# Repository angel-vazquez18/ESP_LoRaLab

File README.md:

# ESP_LoraLab

One repository for the ESP-IDF node firmware and the macOS LoRa laboratory testbed.
One or two physical nodes share one firmware codebase; the host assigns roles A/B.
Local checks work with either node alone. RF tests require two distinct devices.
The dashboard and CLI use the same Python backend and experiment lifecycle.

```text
ESP_LoraLab/
├── AGENTS.md                  Start here for agent-assisted work
├── CONTEXT.md                 Shared domain vocabulary
├── contracts/v2/              Shared defaults, vectors and generated wire schemas
├── firmware/
│   ├── lora_node/             Main node control, health and finite memory diagnostics
│   ├── diagnostic/            Working serial/health diagnostic target
│   └── components/            Planned shared firmware module locations
├── testbed/
│   ├── src/lora_testbed/       Python backend, CLI, physical sessions and analysis
│   ├── frontend/              React/TypeScript dashboard
│   ├── tests/                 Host, procedure and adapter regression checks
│   └── pyproject.toml         Python project and dependency lock beside it
├── hardware/                  Planned wiring, board profile and reference diagram
├── docs/                      Architecture, status, CDR, contracts and procedures
├── scripts/                   Shared generation and verification tools
└── local/                     Ignored local migration artifacts, if present
```

## Start the host

From this repository root:

```sh
make setup
make frontend
make serve
```

Open http://127.0.0.1:8000. For dashboard development use `make frontend-dev`
in another terminal while the backend runs. Requires Python 3.12+, uv and Node/npm.
The host's ignored data directory is `testbed/data/` when started with `make serve`.
Use one backend per data directory and release serial ports before IDF Monitor.

Individual commands from the repository root:

```sh
uv run --project testbed lora-testbed status
uv run --project testbed lora-testbed serial-check --preview
uv run --project testbed lora-testbed preflight IF-02
uv run --project testbed lora-testbed serial-check --role A
```

The host has no simulation mode. Connect each node from Bench overview. The
physical diagnostic check covers only part of IF-01; other experiment runners
remain blocked pending firmware and physical execution support. Historical
records retain their original provenance and exports.

## Build firmware

ESP-IDF v6.0.2, target ESP32-S3. Activate your local installation first:

```sh
source /Users/anken18/.espressif/v6.0.2/esp-idf/export.sh
make firmware-build
```

`make diagnostic-build` builds the existing diagnostic target. These targets only
build; flashing is a separate operator action. Main firmware includes strict serial
control, finite diagnostics, artifact/audio/codec operations and protected finite
radio messages. Board selections and exact live capabilities gate their use;
physical acceptance is still required. See [Milestone 1 review](docs/milestone_1_review.md) and the
[firmware guide](firmware/README.md).

## Verify

```sh
make check
```

This runs all host tests, Ruff, the dashboard production build, generated-contract
consistency and the repository checks. Firmware builds are separate toolchain
checks. See [development workflow](docs/development.md) for exact commands.

## Read next

- [Agent instructions and task routing](AGENTS.md) and [document ownership](docs/agent_workflow.md)
- [Architecture](docs/architecture.md) and [shared vocabulary](CONTEXT.md)
- [GitHub board, issues and acceptance workflow](docs/github_workflow.md)
- [Node development plan](docs/node_development_plan.md): capabilities, milestones and completion evidence
- [Project brief and confirmed decisions](docs/project_brief.md)
- [Current status](docs/status.md) and [23-experiment implementation checklist](docs/experiment_implementation_checklist.md)
- [Hardware wiring](hardware/README.md)
- [Migration and retained local artifacts](docs/migration.md)

The shared local codec API/CLI now preserves source, encoded and decoded files
with independent verification and playback provenance. See
[local codec workflow](docs/codec_provenance.md) for commands and physical checks.

Secure finite voice from a reference or microphone is now available through the
shared Voice dashboard, API and CLI, with labelled equal-encoded-size and
standard64 comparisons.
See [secure voice workflows](docs/secure_voice_workflows.md) for readiness,
commands, retained files and remaining physical acceptance.

Optional [host-armed PTT capture](docs/host_armed_ptt.md) defaults off. Confirm the
printed board revision and GPIO47-to-GND wiring before enabling a physical image.

Optional [OLED status](docs/oled_status.md) shows real node phases through an
isolated worker. It defaults off and requires a verified standard V4 R2
OLED/power map; its USB observation does not qualify physical screen output.

Data and committed encoded voice share the [reserved run lifecycle](docs/run_lifecycle.md):
prepare reserves working memory, both roles arm, sender start has a five-second
window, and cleanup preserves original errors and committed evidence. New RF work
requires matching `finite_message_execution_v3` host/firmware profiles.

Optional [named memory observations](docs/memory_observations.md) collect bounded
10 Hz and stage samples with separate observed minima, requested buffer ownership
and explicit missed/dropped/untracked limits. Physical memory acceptance is pending.

The [fixed-rate encoded source](docs/fixed_rate_source.md) independently produces
8 bytes per 20 ms, bounds all encoded queue content to 4,800 bytes and preserves
actual pacing/drop/drain evidence. It reuses protected multi-message transport;
host procedure controls and sustained-link qualification follow separately.

The [common physical lifecycle](docs/common_physical_lifecycle.md) binds data,
audio/files and diagnostic jobs to an exact USB connection as well as device/boot.
It retains primary versus cleanup failures, committed captures after readback
failure, and durable diagnostic summaries/evidence without automatic resume.

[Physical campaign plans](docs/physical_campaign_plans.md) save typed settings,
repetitions, directions and seeded order with linked batches bounded to 64 cases
and 30 minutes. Preview/save/list/reload work through the API and CLI; campaign
execution and its dashboard remain separate following work.

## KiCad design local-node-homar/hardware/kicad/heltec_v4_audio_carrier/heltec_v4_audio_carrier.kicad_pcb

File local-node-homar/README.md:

# LoRa walkie-talkie

An ESP32 project that records a short voice message, splits it into small packets,
reassembles the packets, and plays the message through a speaker. This is the
audio foundation for a LoRa walkie-talkie.

**Current stage: bringing up two Heltec WiFi LoRa 32 V4.3 / ESP32-S3R2 nodes.**
Packet delivery is still simulated in memory; the firmware does not transmit
over LoRa yet. PTT is deferred until the radio transport works. The Heltec audio
bench holds the SX1262 in reset and disables its RF front end.

### Heltec bench targets

| Node / OLED label | Assigned port | Hardware base MAC | PlatformIO environment |
| --- | --- | --- | --- |
| Heltec-A / COM6 | COM6 | 8C:FD:49:B5:B7:8C | `heltec_v4_com6` |
| Heltec-B / COM7 | COM7 | 44:1B:F6:6F:99:E4 | `heltec_v4_com7` |

Both chips were identified through their ROM bootloader as ESP32-S3 revision
0.2 with 2 MB embedded quad PSRAM and 16 MB flash. COM names are Windows
assignments and can change; match the USB serial number to the MAC above before
uploading. The firmware's OLED label records the assigned bench port.

The default build now selects both Heltec targets. Each uses Rev B wiring:
microphone BCLK/WS/data = GPIO4/6/38; amplifier BCLK/LRC/DIN/SD = GPIO40/41/47/48.
Amplifier SD needs its 1 kOhm pulldown; VIN uses USB 5V. Leave GPS disconnected
and GPIO39/PTT unwired. The built-in OLED uses SDA17/SCL18/reset21 with Vext36;
no external display wiring is needed. These assignments are for standard R2,
not V4-R8.

Current wiring reference: [Rev B schematic](output/schematics/Heltec_V4_R2_Wiring_RevB.svg)
([PNG](output/schematics/Heltec_V4_R2_Wiring_RevB.png)). The original Heltec PDF
and earlier drawings are historical drafts. Heltec speaker output is still
unresolved; the latest checkpoint and remaining connection checks are recorded
in [BENCH_VALIDATION.md](BENCH_VALIDATION.md).

On ESP32-S3, speaker output uses 32-bit stereo I2S slots at 512 kHz BCLK,
with the same 16-bit PCM promoted into the upper 16 bits of each slot. Silent
clocks run before amplifier enable. This avoids the MAX98357A's special 256 kHz
startup mode, which conflicts with the S3 serializer's stopped WS-high state.
The original ESP32 keeps its existing 16-bit stereo / 256 kHz sequence.

```powershell
pio run -e heltec_v4_com6 -e heltec_v4_com7
pio run -e heltec_v4_com6 -t upload
pio run -e heltec_v4_com7 -t upload
python tools/verify_heltec_bench.py --ports COM6 COM7
```

The verification tool keeps both serial connections open, checks identity and
audio readiness, then plays a one-second 1 kHz tone on A, on B, and on both.
It saves per-port logs and a JSON summary under `captures/`. Successful serial
completion proves the digital transfer; listening is still needed to confirm
sound from each speaker. Close other serial monitors before running it.

For silent-speaker diagnosis, the diagnostic firmware adds `v` to report GPIO48
enable readback and measured GPIO40/41 clock-edge counts. After uploading that
build, use `python tools/verify_heltec_bench.py --identify-only --probe-pins`.
Expected clocks are approximately 512 kHz BCLK and 8 kHz LRC, with SD high.
These are measurements at the ESP32 pins; they do not prove the wires reach the
amplifier or that its VIN supply is present. `--tone-repetitions 3` repeats each
node's one-second tone three times before the paired test.

The Heltec `s` tone also reports DIN rising-edge activity on GPIO47. An intact
one-second test pattern has 32,000 rising edges (two transitions per 32-bit
word, two slots per frame, 8,000 frames). This count checks MCU output activity;
it does not decode I2S timing or verify the waveform at the amplifier terminal.
Playback pads its last DMA block with silence to keep subsequent commands on a
descriptor boundary. This avoids losing initial samples after an idle interval;
the requested audio samples and tone duration are unchanged.

For scope capture, firmware revision `audio-bench-7-scope-tone` adds `b` for a
continuous 15-second 1 kHz tone. Use
`python tools/verify_heltec_bench.py --ports COM7 --tone-seconds 15`, or send `b`
through a 115200-baud serial monitor. This revision is uploaded to COM7; COM6
still has the preceding diagnostic revision. The usual `s` remains one second.

Use `pio run -e esp32dev` for the original ESP-WROOM-32 setup described below;
its GPIO assignments remain unchanged. Never upload that binary to a Heltec.

The original hardware setup uses an **ESP-WROOM-32 development board**, an **INMP441
microphone**, and a **MAX98357A amplifier**. The firmware records three-second
clips. On 2026-11-16, the user confirmed clear recorded speech, working speaker
playback, packetized playback, and playback with simulated packet loss. Saved
captures passed format and checksum checks with no clipped samples. One capture
still contains a large low-frequency disturbance; amplifier startup timing also
remains unmeasured. See the latest checkpoint in [BENCH_VALIDATION.md](BENCH_VALIDATION.md).
Successful compilation alone does not establish that the audio hardware works.

Start with sections 1–3 for your first build. Continue with hardware when ready.

- [1. Install the tools](#1-install-the-tools)
- [2. Fork or clone the repository](#2-fork-or-clone-the-repository)
- [3. Build the firmware](#3-build-the-firmware)
- [4. Connect and check the hardware](#4-connect-and-check-the-hardware)
- [5. Upload and try the commands](#5-upload-and-try-the-commands)
- [6. Save recordings on your computer](#6-save-recordings-on-your-computer)
- [7. Run the tests](#7-run-the-tests)
- [8. Find your way around the code](#8-find-your-way-around-the-code)
- [9. Make and contribute a change](#9-make-and-contribute-a-change)
- [Troubleshooting](#troubleshooting)
- [Additional documentation](#additional-documentation)

## 1. Install the tools

You will need an internet connection for the initial downloads and these tools:

| Tool | What it is for |
| --- | --- |
| [Git](https://git-scm.com/install/) | Downloads the repository and records changes to files. |
| [Visual Studio Code](https://code.visualstudio.com/) | The editor used by this guide. |
| [PlatformIO IDE](https://marketplace.visualstudio.com/items?itemName=platformio.platformio-ide) | A VS Code extension that installs the ESP32 build tools and builds/uploads firmware. |
| A GitHub account with repository access | Lets you clone this private repository and contribute changes. |

In VS Code, open **Extensions** with **Ctrl+Shift+X**, search for **PlatformIO
IDE**, and install the extension published by PlatformIO. Allow its setup to
finish, then restart VS Code if prompted. PlatformIO Core, the `pio` command-line
tool, is included with the extension. See the
[official installation guide](https://docs.platformio.org/en/latest/integration/ide/vscode.html#installation)
if setup fails.

The detailed examples below use **Windows and PowerShell**, the environment used
for this project. The Git and `pio` commands also work on macOS/Linux after those
tools are installed. Python alternatives are provided for recording; the included
C++ test launcher is a Windows PowerShell script.

## 2. Fork or clone the repository

A **fork** is your own GitHub copy of a repository. A **clone** is a local copy on
your computer. Use a fork when contributing through your own account, or clone
the original if you are working directly as an authorized collaborator.

This repository is currently private. You must be signed into an account with
access. Forking also depends on the repository's permissions; if **Fork** is
unavailable, ask the owner about access or use an authorized collaborator branch.
[GitHub explains private forks here](https://docs.github.com/en/pull-requests/reference/forks).

1. Open [homarrodriguez/lora-walkie-talkie](https://github.com/homarrodriguez/lora-walkie-talkie).
2. To make your own copy, click **Fork**, select your account, and create the fork.
3. On the repository you will work from, click **Code → HTTPS** and copy its URL.
4. In VS Code, press **Ctrl+Shift+P**, run **Git: Clone**, paste that URL, and choose
   a local folder. Complete GitHub sign-in if prompted, then open the cloned folder.

If you prefer a terminal, the commands for a fork are below. Replace
`YOUR-GITHUB-USERNAME` with your account name before running them:

```sh
git clone https://github.com/YOUR-GITHUB-USERNAME/lora-walkie-talkie.git
cd lora-walkie-talkie
```

To clone the original repository, use `homarrodriguez` in place of the placeholder.
If you already have a local copy, open that folder instead of cloning again.

**Open the folder containing `platformio.ini` in VS Code.** This is the project
root: run the commands in this guide from that folder. A folder named
`esp32-audio-chunker-test` from an earlier local setup works too; the name of the
local folder does not affect the build.

## 3. Build the firmware

**Firmware** is the program that will run on the ESP32. Building compiles the
source files into firmware; uploading later writes it to the board. Building
does not require a board or change a connected board.

1. Open **Ctrl+Shift+P → PlatformIO: New Terminal**.
2. Confirm the terminal is in the project root.
3. Run:

```sh
pio run -e esp32dev
```

The first build downloads the platform, compiler, and framework and can take a
few minutes. A successful build ends with **`[SUCCESS]`**. Generated files go in
`.pio/`, which Git ignores. PlatformIO also generates your local VS Code settings.

An **environment** is a named build configuration in `platformio.ini`. This
project provides four:

| Environment | Enabled hardware | When to use it |
| --- | --- | --- |
| `esp32dev` | Microphone and amplifier | Full recording and playback tests on the original ESP-WROOM-32. |
| `mic_only` | Microphone only | Diagnose capture with amplifier SD held low and speaker I2S disabled. |
| `speaker_only` | Amplifier only | Check the speaker without initializing the microphone. |
| `serial_only` | Neither audio device | Check the USB serial connection and packet handling. |

To build all four:

```sh
pio run -e esp32dev -e mic_only -e speaker_only -e serial_only
```

The project pins `espressif32@8.0.0`; these original-board environments
target the `esp32dev` board with the Arduino framework. The installed baseline
uses Arduino-ESP32 3.3.12 and ESP-IDF 5.5.5. Keep the supplied `platformio.ini`
for your first build so you start from the same configuration.

If PowerShell cannot find `pio`, use PlatformIO's terminal or its full Windows
path. For example:

```powershell
& "$env:USERPROFILE\.platformio\penv\Scripts\pio.exe" run -e esp32dev
```

After a successful build, you can go straight to [the tests](#7-run-the-tests)
or [the code guide](#8-find-your-way-around-the-code) if you have no hardware yet.

## 4. Connect and check the hardware

For the full audio setup, you need an ESP-WROOM-32 development board, a USB
**data** cable, an INMP441 microphone, a MAX98357A amplifier, a suitable speaker,
jumpers, and a 1 kOhm resistor. The development bench uses an 8-ohm, 1-watt speaker.
No LoRa radio module is required for the current firmware.

**Disconnect power before wiring.** Use GPIO numbers printed on the board, not
header positions. This pin map is for the original ESP-WROOM-32 setup; other
ESP32 variants or boards need their own schematic and pin checks.
GPIO means a programmable input/output pin. Connect all module GND pins to the
ESP32's ground so the devices share the same electrical reference.

| Device | Pin | Connect to |
| --- | --- | --- |
| INMP441 microphone | VDD | ESP32 3V3 |
| INMP441 microphone | GND | Common GND |
| INMP441 microphone | SCK / BCLK | GPIO26 |
| INMP441 microphone | WS | GPIO25 |
| INMP441 microphone | SD (audio data) | GPIO33 |
| INMP441 microphone | L/R | GND, selecting the left channel |
| MAX98357A amplifier | VIN | Verified regulated 5 V supply, as described in the bench guide |
| MAX98357A amplifier | GND | Common GND |
| MAX98357A amplifier | BCLK | GPIO14 |
| MAX98357A amplifier | LRC / WS | GPIO16 |
| MAX98357A amplifier | DIN | GPIO17 |
| MAX98357A amplifier | SD / MODE (enable) | GPIO27, with a 1 kOhm resistor from SD to GND |
| MAX98357A amplifier | GAIN | GND for the documented bench setup |
| Speaker | Two leads | Amplifier SPK+ and SPK− |
| Optional push-to-talk button | Switch contacts | GPIO4 and GND; leave disabled initially |

The microphone's **SD** is its audio output; the amplifier's **SD** enables or
disables the amplifier. They have different jobs and use different GPIO pins.
Keep amplifier SD off the 3V3 rail: this firmware drives GPIO27 low during
startup. Power the microphone from 3.3 V. Neither speaker lead connects to GND.

Read [BENCH_VALIDATION.md](BENCH_VALIDATION.md) before powering the audio setup.
It includes continuity, power, and oscilloscope checks, including the required
SD pulldown check while reset is held. Some observations in that file describe
earlier firmware; the current source banner is `audio-bench-7-scope-tone`.
See the Heltec checkpoint above for the revisions last uploaded to each node.

## 5. Upload and try the commands

Work through the three environments in order so a wiring problem is easier to
locate. When changing wiring, unplug power first. A disabled driver does not
electrically disconnect a module.

### Start with the board alone

Connect the ESP32 to USB with both audio modules disconnected. Close any serial
monitor or recording console already using the board. Find its serial port:

```sh
pio device list
```

On Windows, the result is usually a name such as `COM4`; on macOS/Linux it may
look like `/dev/cu.usbserial-...` or `/dev/ttyUSB0`. **Replace `COM4` in every
example with your board's actual port.** If several devices appear, compare the
list before and after plugging in the ESP32.

Upload the serial-only build, then open the serial monitor:

```sh
pio run -e serial_only -t upload --upload-port COM4
pio device monitor -p COM4 -b 115200
```

The monitor displays text sent over USB. `115200` is the baud rate, or connection
speed, and must match the firmware. Press the board's reset button if you missed
the startup banner. Send `i` to inspect the system, then `t` to test packet
reassembly. Expect **`[TEST] PASS: 200 packets reassembled correctly`**.
Close the monitor with **Ctrl+C** before another program uses the port.

### Add the speaker, then the microphone

With power removed, connect and check the amplifier and speaker. Upload the
speaker-only build, reopen the monitor, and send `s`:

```sh
pio run -e speaker_only -t upload --upload-port COM4
pio device monitor -p COM4 -b 115200
```

Listen for a one-second tone. The digital completion message means the software
sent the audio; hearing the tone is a separate check. Follow the bench guide if
it is silent.

After the speaker checks pass, unplug power, add the microphone, and upload the
full build:

```sh
pio run -e esp32dev -t upload --upload-port COM4
pio device monitor -p COM4 -b 115200
```

Send `m`, wait for **Speak now**, and speak for three seconds. Next try `r` for
direct playback and `p` for playback after simulated packet delivery. Send one
command at a time and wait for the operation to finish.

### Firmware command reference

These are single-letter commands entered in the ordinary serial monitor.

| Command | What happens |
| --- | --- |
| `i` | Prints firmware versions, uptime, available memory, pins, and audio readiness. |
| `t` | Tests reassembly of 200 packets arriving in reverse order; replaces the saved recording buffer. |
| `s` | Plays a one-second, 1 kHz speaker test tone. |
| `m` | Records a three-second clip and prints microphone statistics. |
| `r` | Records a clip and plays it directly through the speaker. |
| `p` | Records, packetizes, simulates delivery, verifies the result, and plays it. |
| `l` | Toggles loss simulation for `p`: zero lost chunks or 11 lost chunks, replaced by silence. |
| `x` | Prints the packet format. |
| `h` | Toggles the once-per-second heartbeat/status message. |
| `d` | Sends binary audio; use the recording tools below rather than a text monitor. |

Both `esp32dev` and `mic_only` support microphone recording; use `m` and `d`
with `mic_only` because speaker playback is disabled. The optional
push-to-talk button is disabled by `Config::ENABLE_PTT = false`. Once wired and
enabled, one press triggers the same sequence as `p`, recording a fixed
three-second clip even if the button stays held.

## 6. Save recordings on your computer

The **recording console** is a Python program on your computer. It asks the ESP32
to record, retrieves the audio over USB, and saves files you can listen to or
inspect. The firmware keeps its recording in RAM (temporary memory); it does not write a WAV file
on the ESP32. Resetting the board loses that recording.

Upload `esp32dev` and close the ordinary serial monitor first. From PowerShell
in the project root, run:

```powershell
& "$env:USERPROFILE\.platformio\penv\Scripts\python.exe" -u .\tools\record_monitor.py --port COM4
```

This uses PlatformIO's Python environment, which includes the `pyserial` library
for USB serial communication. The Windows shortcut is
`.\tools\record-monitor.ps1 -Port COM4` if PowerShell permits scripts.
On macOS/Linux, use PlatformIO's Python at `~/.platformio/penv/bin/python` with
`tools/record_monitor.py` and your actual serial port.

At the `record>` prompt, enter a command and press Enter:

| Console command | Result |
| --- | --- |
| `m quiet` | Records and saves a clip labeled `quiet`, without playing it. |
| `m speech` | Records and saves a clip labeled `speech`. |
| `r playback_check` | Records, plays that clip on the ESP32 speaker, and saves the same clip. |
| `d saved-earlier` | Saves the last valid recording without recording again. |
| `q` | Exits and releases the serial port. |

Labels are optional. Wait for **Speak now**, then wait for **SAVED** before
entering the next command. Recording takes three seconds; exporting adds about
five seconds. These labeled commands belong in the Python console, not the
ordinary serial monitor.

Each successful capture creates a new folder under `captures/`:

```text
captures/<timestamp>-speech/
    recording.wav         Audio at its original volume: 8 kHz, 16-bit mono
    recording.json        Measurements, label, timestamps, and checksum
    recording.svg         Waveform you can open in a browser
    recording.serial.txt  Text diagnostics from the ESP32
```

The tool checks the expected byte count and a CRC-32 checksum, a value used to
detect transfer corruption. It never overwrites an existing capture. Failed
attempts retain an `error.json` file and a log; they do not produce a valid WAV.
Listen to the WAV at a low initial volume and compare it with speaker playback.

For a single capture that saves and exits automatically, append `--once speech`
to the Python command above. The separate `tools/capture_audio.py` utility also
supports one-shot export; run it with `--help` to see its options.

Saved recordings are included in this private repository. Review new recordings
before committing them, especially if they contain personal conversations.

## 7. Run the tests

**Host tests** run on your computer without an ESP32. They check software behavior
using substitute hardware calls. They cannot confirm wiring, sound quality, or
physical signal timing.

### Python tests

From the project root in PowerShell:

```powershell
& "$env:USERPROFILE\.platformio\penv\Scripts\python.exe" .\test\host\capture_audio_test.py
& "$env:USERPROFILE\.platformio\penv\Scripts\python.exe" .\test\host\record_monitor_test.py
& "$env:USERPROFILE\.platformio\penv\Scripts\python.exe" .\test\host\heltec_bench_test.py
```

Each should finish with **`OK`**. They cover audio export parsing, checksum
failures, incomplete transfers, recording-console behavior, and saved files.
On other operating systems, run the same files with Python 3.

### C++ tests on Windows

These need a C++ compiler that builds programs for your computer. PlatformIO's
ESP32 compiler builds programs for the board, so install a host compiler too.

Install [MSYS2](https://www.msys2.org/), follow its initial setup, then open the
**MSYS2 UCRT64** terminal from the Start menu and run:

```sh
pacman -S mingw-w64-ucrt-x86_64-gcc
```

This is the [official MinGW-w64 setup](https://www.mingw-w64.org/getting-started/msys2/).
Return to PowerShell in the project root and run:

```powershell
.\test\host\run.ps1
```

The runner expects `C:\msys64\ucrt64\bin\g++.exe`. If your compiler is installed
elsewhere, pass its path:

```powershell
.\test\host\run.ps1 -Compiler 'C:\your-compiler-folder\bin\g++.exe'
```

Expect `PASS` messages and no compilation or test failures. The runner checks
packet ordering, duplicates, invalid packets, missing-chunk silence, audio sample
conversion, partial/failed I/O, and amplifier startup/error handling. It tests
audio behavior with all four environment settings. Temporary executables go in
the Git-ignored `.host-test/` directory.

## 8. Find your way around the code

| File or folder | Start here when you want to… |
| --- | --- |
| `platformio.ini` | Change the board, build environments, or build settings. |
| `src/main.cpp` | Follow startup, serial commands, and the record/packetize/play sequence. |
| `lib/audio/audio_manager.cpp` and `.h` | Work on microphone capture, speaker playback, and amplifier initialization. |
| `lib/chunking/chunker.cpp` and `.h` | Work on packet creation and receive assembly. |
| `include/config.h` | Inspect audio format, gain, buffer sizes, protocol constants, and PTT enablement. |
| `include/pins.h` | Inspect or adapt GPIO assignments for verified hardware. |
| `include/protocol.h` | Inspect the packet header and validation rules. |
| `include/audio_diagnostics.h` | Find the CRC-32 helper used by audio export. |
| `tools/` | Work on the PC recording tools or the IDE include-path workaround. |
| `test/host/` | Run or extend software tests and hardware substitutes. |
| `captures/` | Inspect saved bench recordings and diagnostic logs. |
| `exports/` | Find the archived project ZIP and its checksum; use the checked-out source for current development. |

### How a voice message moves through the program

The microphone produces digital audio over **I2S**, the interface connecting the
audio modules to the ESP32. The firmware stores it as **PCM**, a sequence of
signed numbers representing the sound waveform.

```text
Microphone -> PCM recording -> 200 packets -> simulated delivery
           -> indexed reassembly -> speaker playback
```

At 8,000 samples per second, a three-second recording contains 24,000 samples.
Each 16-bit sample occupies two bytes, giving a 48,000-byte recording. A packet
contains a seven-byte header and 240 bytes of audio, for 247 bytes total. The
receiver places each payload at its chunk index, so packets can arrive out of
order. Missing chunks remain zeros, which play as silence.

### Constraints to preserve when changing the code

- **Buffer lifetime:** the transmit buffer uses 48,000 bytes; each `VoiceChunker`
  owns another 48,000-byte receive buffer. Keep them in long-lived storage, not
  local variables on a small ESP32 task stack. `beginTransmit()` borrows its
  buffer; keep that audio unchanged until packet creation finishes.
- **Packet compatibility:** version 1 expects exactly 200 full chunks. Changes
  to sample rate, recording duration, or payload size affect buffer sizing and
  protocol rules together. Header checks and compile-time assertions enforce
  the current format.
- **Receive ownership:** a differing message ID resets assembly. That is suitable
  for the local simulation but must be addressed before accepting packets from
  multiple or delayed senders. The packet format itself has no CRC field; the
  serial-export CRC checks a separate transfer.
- **Audio ownership:** the current operations block until finished and share
  buffers. Avoid calling them concurrently or from interrupt handlers. Capture
  uses legacy I2S port 0; playback uses port 1.
- **Amplifier timing:** preserve the SD startup sequence and continuous speaker
  clocks. `stopSpeaker()` clears queued audio while keeping the clocks running.
  Changing this behavior requires the electrical checks in the bench guide.

## 9. Make and contribute a change

Create a branch before editing. A branch keeps your work separate from `main`:

```sh
git switch -c improve-recording-docs
```

Choose a name that describes your work. If you use a fork, add the original
repository as `upstream` once so you can bring in later changes:

```sh
git remote add upstream https://github.com/homarrodriguez/lora-walkie-talkie.git
```

Use `git remote -v` to check existing remotes before adding one. `origin` normally
points to the repository you cloned; for a fork, it should point to your fork.

Make a small, focused change. For firmware changes, build the affected
environments and run the relevant tests above. For hardware changes, also record
the wiring and bench checks you performed. Review your changes before saving
them in Git:

```sh
git status
git diff
```

For example, after editing only the README:

```sh
git add README.md
git commit -m "Clarify recording setup"
git push -u origin improve-recording-docs
```

`git add` selects files, `git commit` saves a local revision, and `git push`
uploads it. Use the actual filenames and branch name for your change. If Git
asks for an author identity, set it for this repository, replacing the examples:

```sh
git config user.name "Your Name"
git config user.email "YOUR-GIT-COMMIT-EMAIL"
```

You can use the no-reply address shown in your GitHub email settings. If the
commit failed because your identity was missing, run it again after setting it. After
pushing, open GitHub and create a **pull request**: a request to review and merge
your branch into the original repository's `main`. Describe the change, the
commands you tested, and any hardware results.

Keep `.pio/`, `.host-test/`, Python caches, and generated VS Code settings out of
commits. `.gitignore` already handles those. Capture files and archived ZIPs are
tracked, so select them deliberately when they are part of your change.

## Troubleshooting

| Problem | First thing to check |
| --- | --- |
| GitHub says “Repository not found” | Sign into an account with access to this private repo and verify the clone URL. |
| `git` or `pio` is not recognized | Restart VS Code after installing Git; use **PlatformIO: New Terminal** for `pio` or the full path shown above. |
| No serial port appears | Try a USB data cable and another USB port. Check the board's USB-to-serial driver requirements. |
| Upload or recording says the port is busy | Close every other serial monitor or recording console. Only one program can use the port at a time. |
| Firmware reports that an audio device is unavailable | Check which environment was uploaded, then inspect `i` and the startup error messages. `serial_only` intentionally disables both devices. |
| Tone transfer completes but there is no sound | Follow the amplifier power, SD, wiring, and speaker checks in `BENCH_VALIDATION.md`. |
| Microphone is silent, noisy, or clipped | Check its 3.3 V supply, ground, L/R selection, and data wiring. Compare an exported WAV with speaker playback before changing gain. |
| Python reports `No module named serial` | Use PlatformIO's Python executable from section 6. A separate Python environment needs the `pyserial` package. |
| A PowerShell `.ps1` script is blocked | Use the direct Python recording command. For the trusted C++ test script, a process-only invocation is `powershell -NoProfile -ExecutionPolicy Bypass -File .\test\host\run.ps1`. |
| C++ tests cannot find `g++.exe` | Install the MSYS2 UCRT64 compiler, or pass its actual location with `-Compiler`. |
| VS Code reports missing include paths | Keep `tools/filter_ide_includes.py` and its `extra_scripts` entry in `platformio.ini`. Run **PlatformIO: Rebuild IntelliSense Index**, then reload the window if old messages remain. |

The IDE hook filters two known missing framework directories whenever PlatformIO
generates editor settings. It does not change normal compilation. Edit
`platformio.ini` and the project scripts for lasting configuration changes;
PlatformIO regenerates `.vscode/c_cpp_properties.json`.

When reporting a problem, include the command you ran, the full error text,
the selected environment, your board model, and relevant startup output. For
audio problems, include the capture label and measurements if available.

### Isolate a noisy microphone recording

The `m` command skips playback, but in the full build the amplifier remains
enabled and speaker clocks continue running. To test capture with amplifier SD
held low and the speaker I2S driver disabled, close the serial monitor and
recording tool, then upload this diagnostic build (replace `COM4` as needed):

```sh
pio run -e mic_only -t upload --upload-port COM4
```

Keep the existing wiring, including amplifier SD on GPIO27. Reopen the Python
recording tool from section 6. Run `m quiet_mic_only` while quiet, wait for
`SAVED`, then `m voice_mic_only` while speaking normally. Compare these WAV files
with the full-build recordings. A clean result implicates interaction with the
enabled speaker path; it does not by itself identify the electrical cause.
Persistent corruption still requires checking microphone power, connections,
I2S capture, and the microphone module. This build leaves the amplifier physically
connected to power, so it is not a complete electrical disconnection test.

To restore recording and speaker playback, close the recording tool and upload
`esp32dev` again with `pio run -e esp32dev -t upload --upload-port COM4`.

## Additional documentation

- [BENCH_VALIDATION.md](BENCH_VALIDATION.md): detailed electrical checks and audio
  acceptance steps, including historical bench observations.
- [README_HANDOFF.md](README_HANDOFF.md): snapshot and component-integration
  details for moving this code into another project.
- [INTEGRATION_PROMPT.md](INTEGRATION_PROMPT.md): a reusable instruction prompt
  for integrating the components into an existing repository.

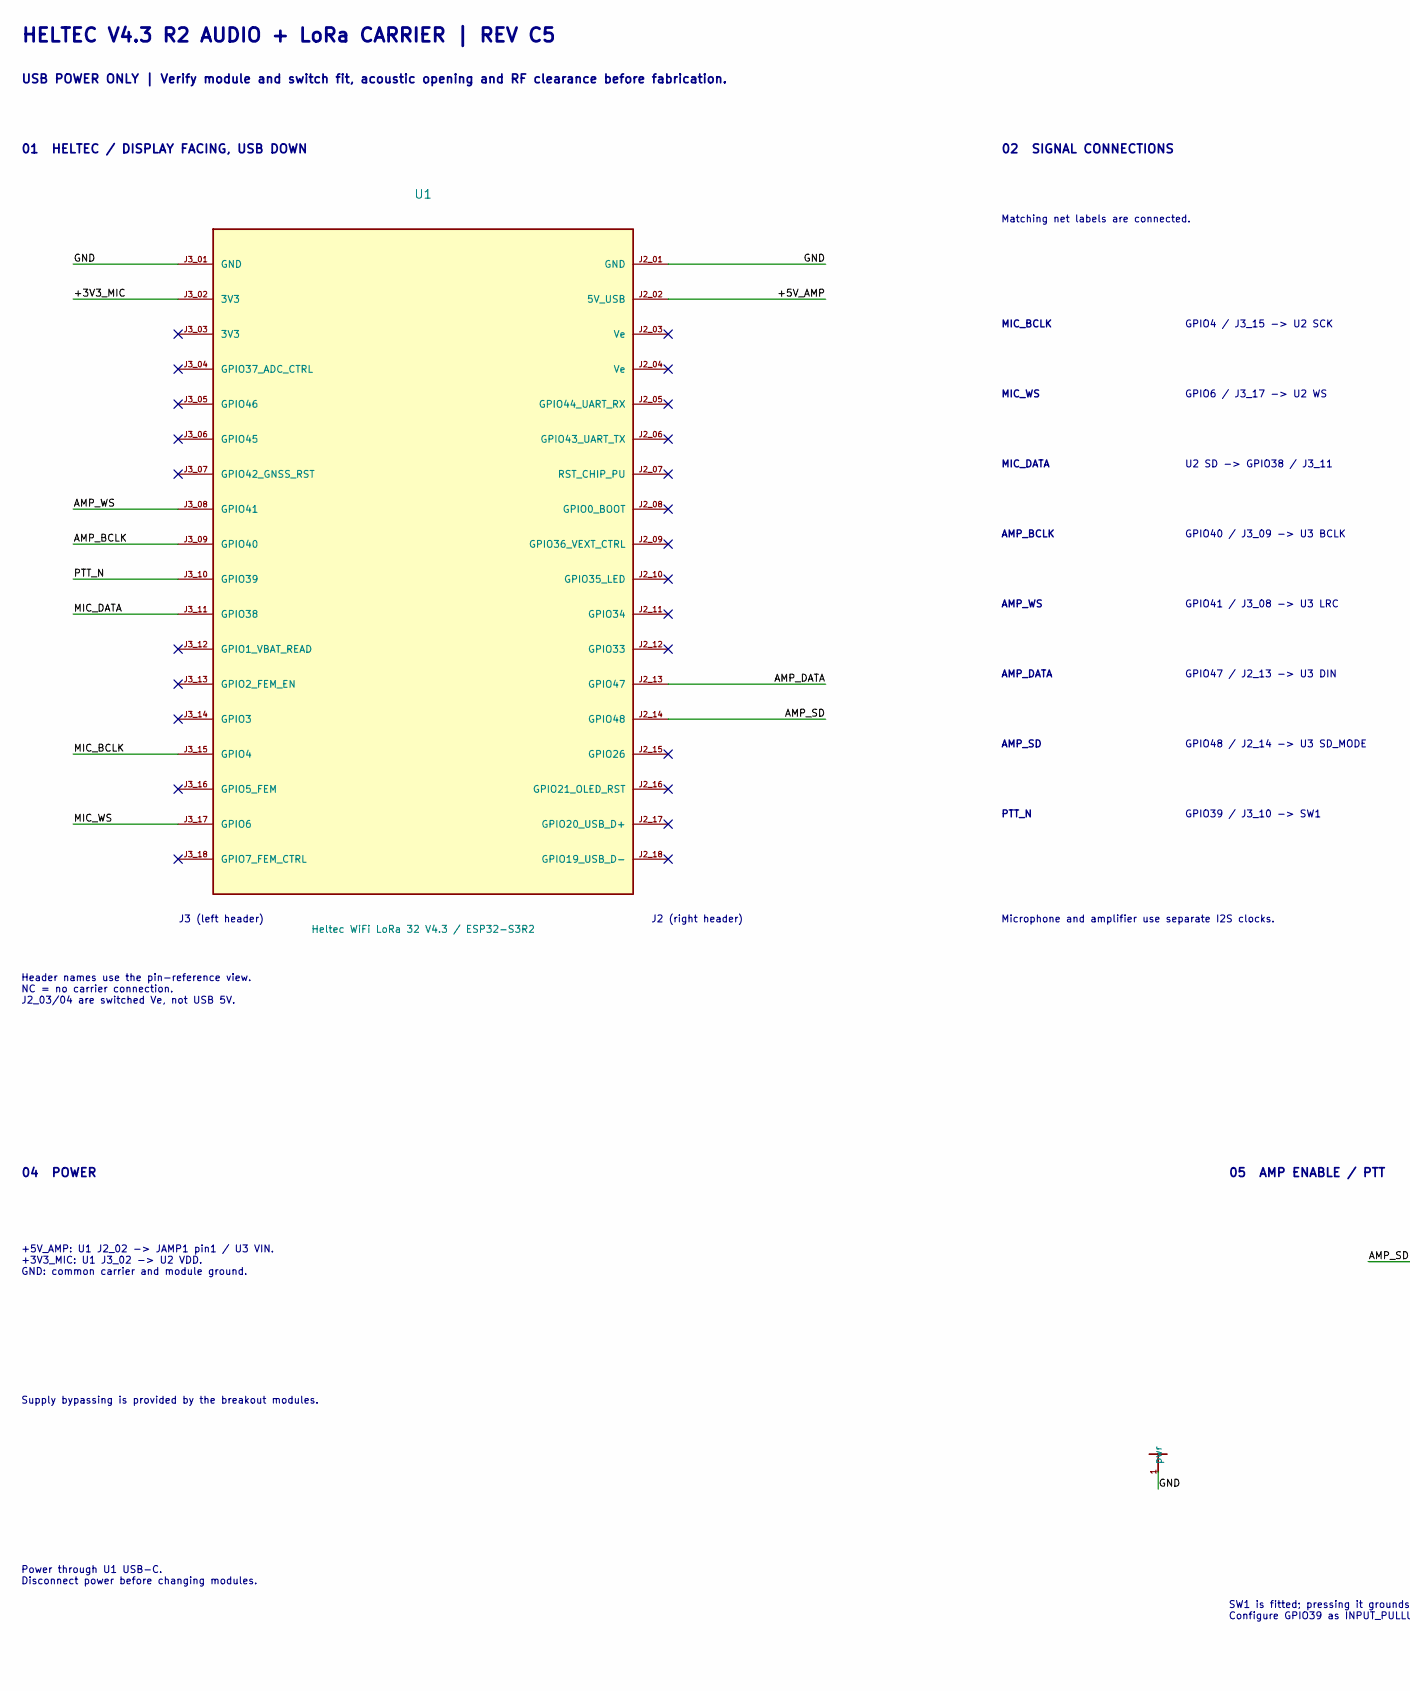
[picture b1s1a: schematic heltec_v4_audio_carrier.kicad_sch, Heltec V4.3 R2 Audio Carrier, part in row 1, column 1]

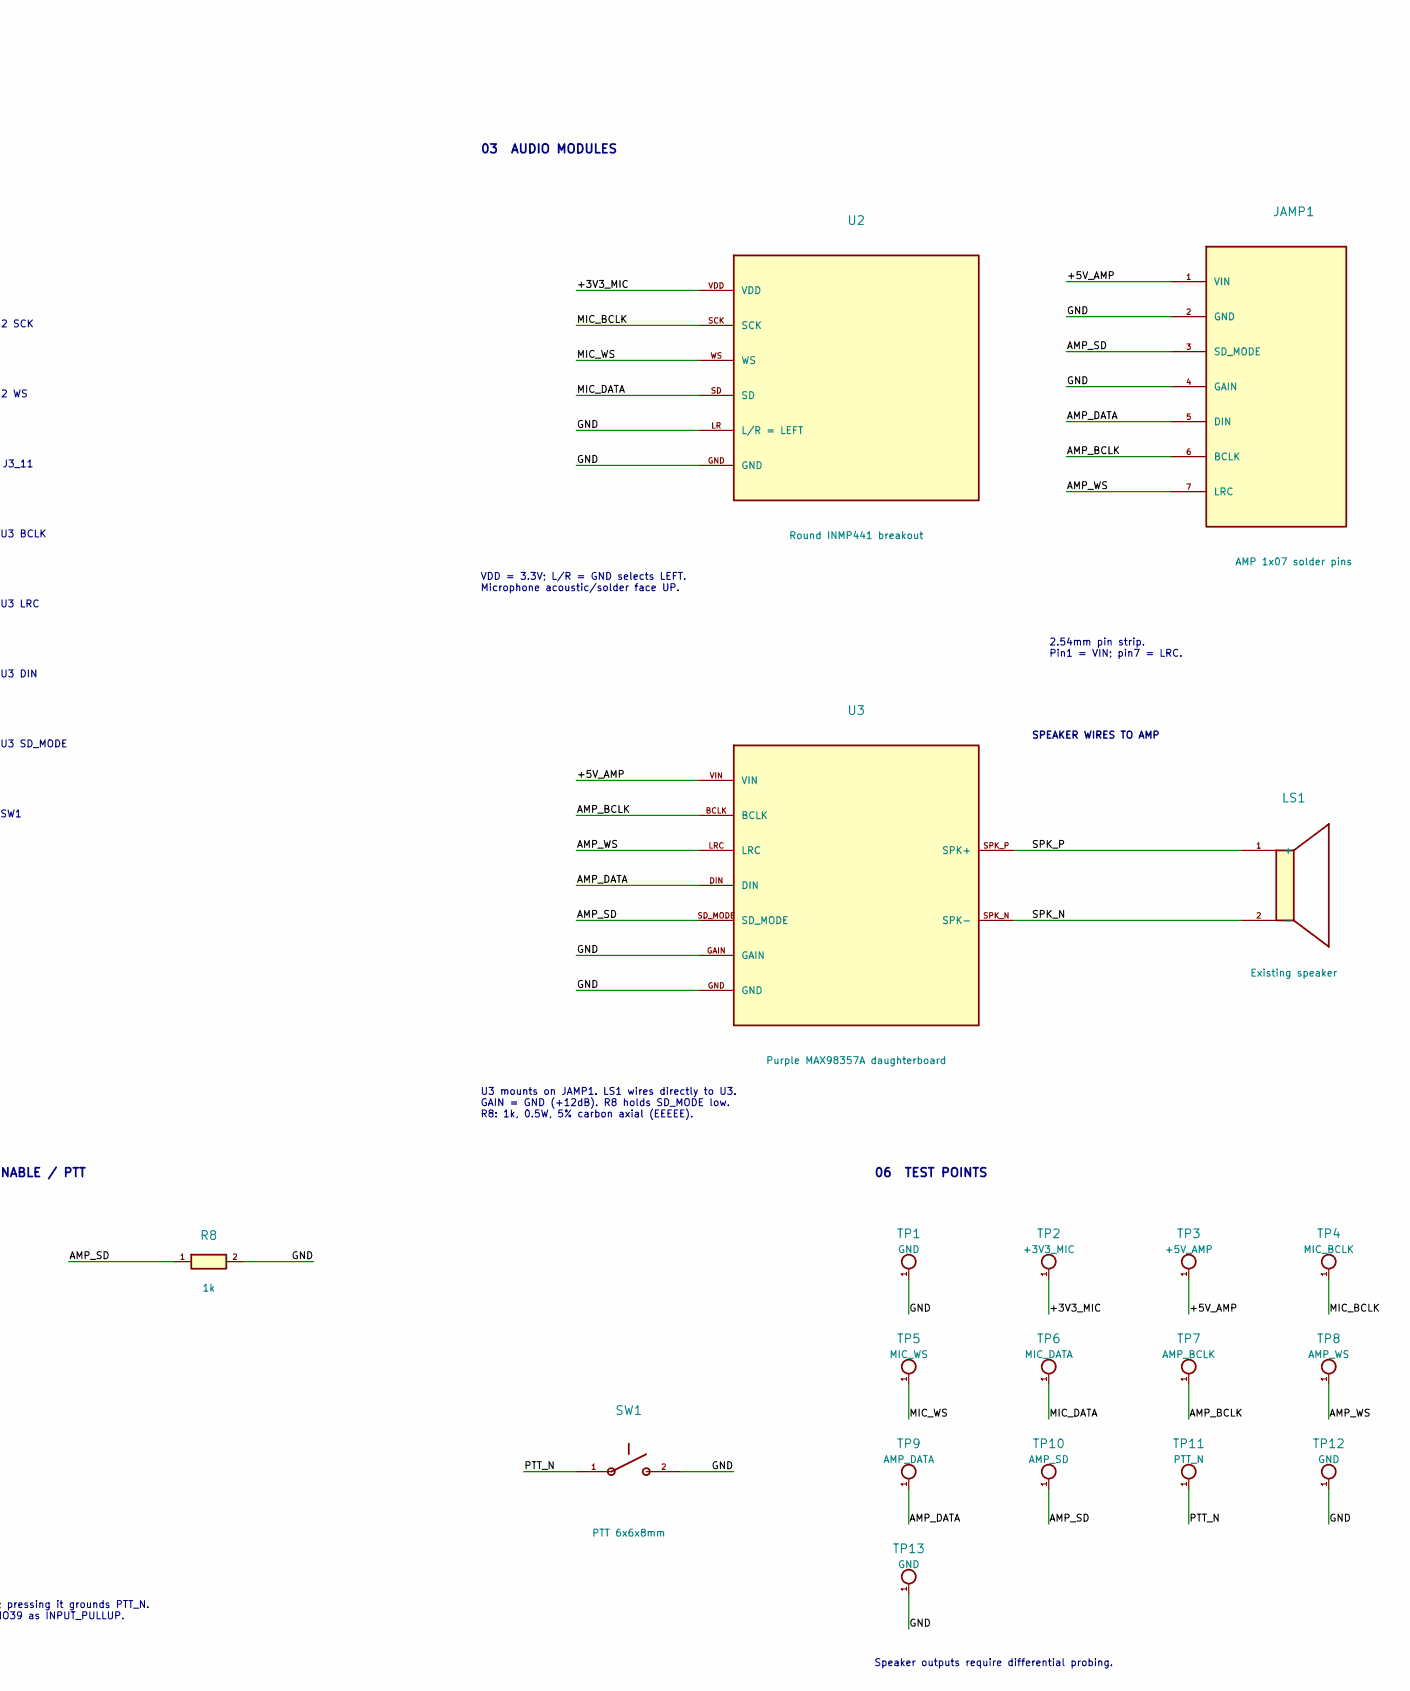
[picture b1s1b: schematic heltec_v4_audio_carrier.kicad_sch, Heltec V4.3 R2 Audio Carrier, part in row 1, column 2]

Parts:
JAMP1: AMP 1x07 solder pins; MAX98357A_H7_2p54_PROVISIONAL; Rating 2.54mm pitch soldered pin strip; suppli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
LS1: Existing speaker; Rating 8 ohm nominal; verify actual speaker po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
R8: 1k; R_Axial_Carbon_0p5W_P15p24_Horizontal; Rating EEEEE carbon axial; 0.5W; 5%
SW1: PTT 6x6x8mm; SW_TACTILE_6x6x8_REFERENCE_FIT_PENDING; Rating Exact switch contact rating pending ver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
TP1, TP12, TP13: GND; TestPoint_Pad_D1.5mm
TP2: +3V3_MIC; TestPoint_Pad_D1.5mm
TP3: +5V_AMP; TestPoint_Pad_D1.5mm
TP4: MIC_BCLK; TestPoint_Pad_D1.5mm
TP5: MIC_WS; TestPoint_Pad_D1.5mm
TP6: MIC_DATA; TestPoint_Pad_D1.5mm
TP7: AMP_BCLK; TestPoint_Pad_D1.5mm
TP8: AMP_WS; TestPoint_Pad_D1.5mm
TP9: AMP_DATA; TestPoint_Pad_D1.5mm
TP10: AMP_SD; TestPoint_Pad_D1.5mm
TP11: PTT_N; TestPoint_Pad_D1.5mm
U1: Heltec WiFi LoRa 32 V4.3 / ESP32-S3R2; Heltec_V4_R2_2x18_PROVISIONAL
U2: Round INMP441 breakout; INMP441_ROUND_2p54x7p62_REFERENCE
U3: Purple MAX98357A daughterboard

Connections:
/+3V3_MIC: TP2.1, U1.J3_02 (3V3), U2.VDD
/+5V_AMP: JAMP1.1 (VIN), TP3.1, U1.J2_02 (5V_USB), U3.VIN
/AMP_BCLK: JAMP1.6 (BCLK), TP7.1, U1.J3_09 (GPIO40), U3.BCLK
/AMP_DATA: JAMP1.5 (DIN), TP9.1, U1.J2_13 (GPIO47), U3.DIN
/AMP_SD: JAMP1.3 (SD_MODE), R8.1, TP10.1, U1.J2_14 (GPIO48), U3.SD_MODE
/AMP_WS: JAMP1.7 (LRC), TP8.1, U1.J3_08 (GPIO41), U3.LRC
/GND: JAMP1.2 (GND), JAMP1.4 (GAIN), R8.2, SW1.2, TP1.1, TP12.1, TP13.1, U1.J2_01 (GND), U1.J3_01 (GND), U2.GND, U2.LR (L/R = LEFT), U3.GAIN, U3.GND
/MIC_BCLK: TP4.1, U1.J3_15 (GPIO4), U2.SCK
/MIC_DATA: TP6.1, U1.J3_11 (GPIO38), U2.SD
/MIC_WS: TP5.1, U1.J3_17 (GPIO6), U2.WS
/PTT_N: SW1.1, TP11.1, U1.J3_10 (GPIO39)
unnamed: LS1.1 (+), U3.SPK_P (SPK+)
unnamed: LS1.2 (-), U3.SPK_N (SPK-)

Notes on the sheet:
HELTEC V4.3 R2 AUDIO + LoRa CARRIER | REV C5
USB POWER ONLY | Verify module and switch fit, acoustic opening and RF clearance before fabrication.
01 HELTEC / DISPLAY FACING, USB DOWN
J3 (left header)
J2 (right header)
Header names use the pin-reference view. NC = no carrier connection. J2_03/04 are switched Ve, not USB 5V.
02 SIGNAL CONNECTIONS
Matching net labels are connected.
MIC_BCLK
GPIO4 / J3_15 -> U2 SCK
MIC_WS
GPIO6 / J3_17 -> U2 WS
MIC_DATA
U2 SD -> GPIO38 / J3_11
AMP_BCLK
GPIO40 / J3_09 -> U3 BCLK
AMP_WS
GPIO41 / J3_08 -> U3 LRC
AMP_DATA
GPIO47 / J2_13 -> U3 DIN
AMP_SD
GPIO48 / J2_14 -> U3 SD_MODE
PTT_N
GPIO39 / J3_10 -> SW1
Microphone and amplifier use separate I2S clocks.
03 AUDIO MODULES
VDD = 3.3V; L/R = GND selects LEFT. Microphone acoustic/solder face UP.
2.54mm pin strip. Pin1 = VIN; pin7 = LRC.
SPEAKER WIRES TO AMP
U3 mounts on JAMP1. LS1 wires directly to U3. GAIN = GND (+12dB). R8 holds SD_MODE low. R8: 1k, 0.5W, 5% carbon axial (EEEEE).
04 POWER
+5V_AMP: U1 J2_02 -> JAMP1 pin1 / U3 VIN. +3V3_MIC: U1 J3_02 -> U2 VDD. GND: common carrier and module ground.
Supply bypassing is provided by the breakout modules.
Power through U1 USB-C. Disconnect power before changing modules.
05 AMP ENABLE / PTT
SW1 is fitted; pressing it grounds PTT_N. Configure GPIO39 as INPUT_PULLUP.
06 TEST POINTS
Speaker outputs require differential probing.

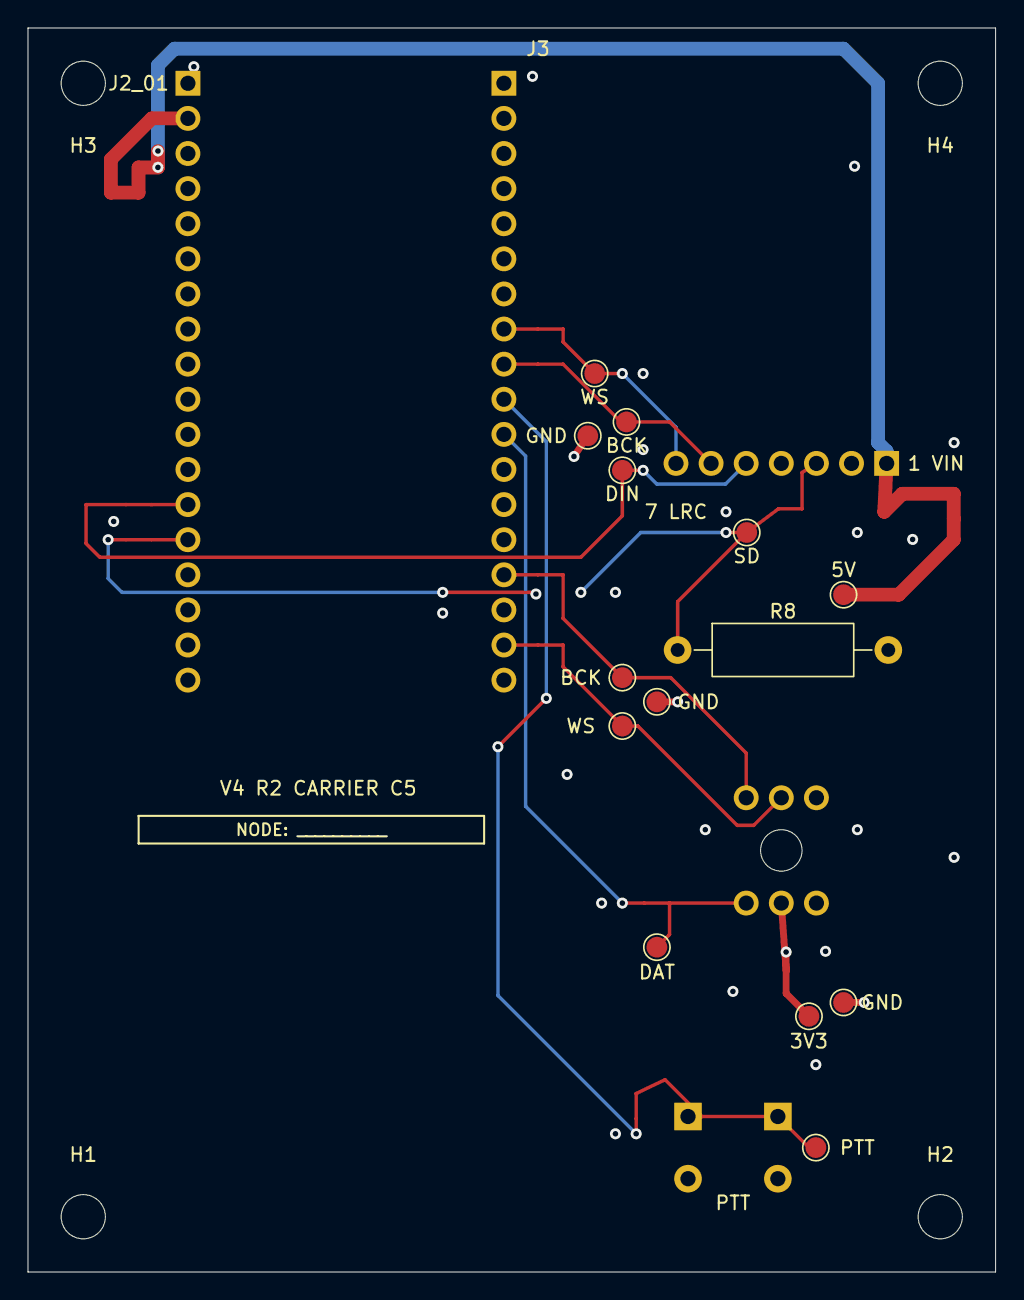
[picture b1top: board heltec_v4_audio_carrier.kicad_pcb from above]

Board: 4 copper layers, 70.0 x 90.0 mm, 22 parts (0 on the bottom side), 11 nets.

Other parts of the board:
H1, H2, H3, H4: M3 NPTH / 7mm hardware clearance
